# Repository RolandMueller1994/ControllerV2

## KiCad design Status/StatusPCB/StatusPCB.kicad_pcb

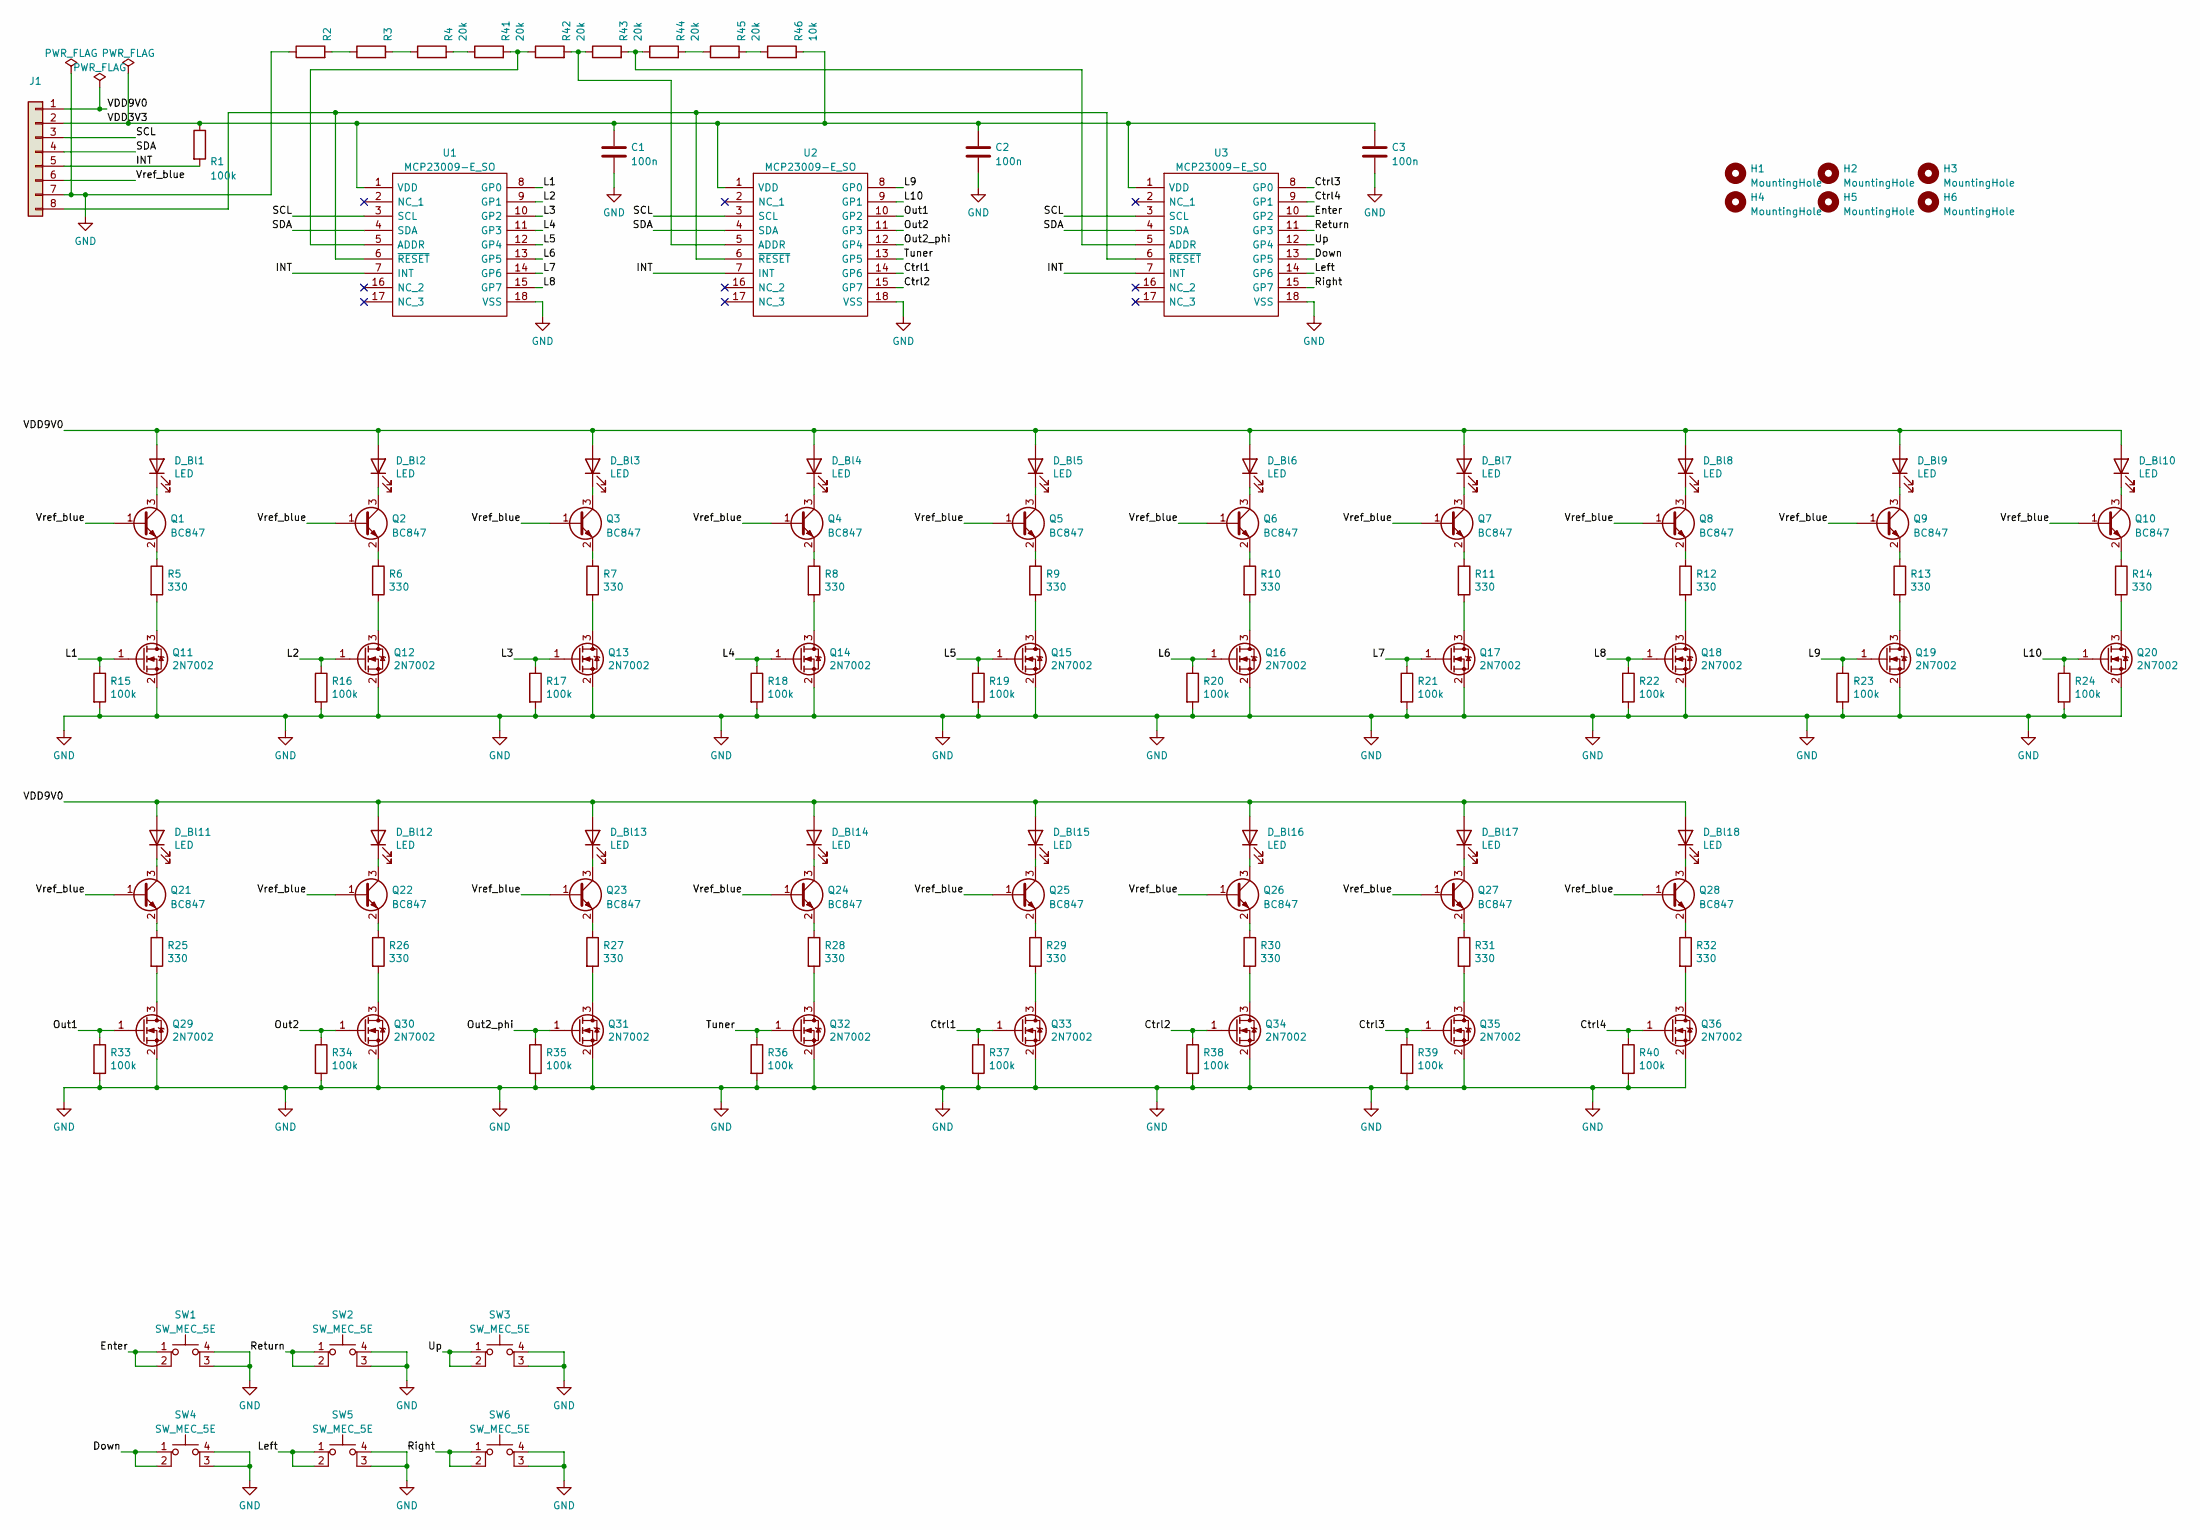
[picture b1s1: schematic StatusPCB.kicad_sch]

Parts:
C1, C2, C3: 100n; C_1206_3216Metric_Pad1.33x1.80mm_HandSolder
D_Bl1, D_Bl2, D_Bl3, D_Bl4, D_Bl5, D_Bl6, D_Bl7, D_Bl8, D_Bl9, D_Bl10, D_Bl11, D_Bl12, D_Bl13, D_Bl14, D_Bl15, D_Bl16, D_Bl17, D_Bl18: LED; LED_D3.0mm
H1, H2, H3, H4, H5, H6: MountingHole; MountingHole_3.2mm_M3
J1: (no value)
Q1, Q2, Q3, Q4, Q5, Q6, Q7, Q8, Q9, Q10, Q21, Q22, Q23, Q24, Q25, Q26, Q27, Q28: BC847; SOT-23
Q11, Q12, Q13, Q14, Q15, Q16, Q17, Q18, Q19, Q20, Q29, Q30, Q31, Q32, Q33, Q34, Q35, Q36: 2N7002; SOT-23
R1, R15, R16, R17, R18, R19, R20, R21, R22, R23, R24, R33, R34, R35, R36, R37, R38, R39, R40: 100k; R_1206_3216Metric_Pad1.30x1.75mm_HandSolder
R2, R3: R_1206_3216Metric_Pad1.30x1.75mm_HandSolder
R4, R41, R42, R43, R44, R45: 20k; R_1206_3216Metric_Pad1.30x1.75mm_HandSolder
R5, R6, R7, R8, R9, R10, R11, R12, R13, R14, R25, R26, R27, R28, R29, R30, R31, R32: 330; R_1206_3216Metric_Pad1.30x1.75mm_HandSolder
R46: 10k; R_1206_3216Metric_Pad1.30x1.75mm_HandSolder
SW1, SW2, SW3, SW4, SW5, SW6: SW_MEC_5E; SW_MEC_5GTH9
U1, U2, U3: MCP23009-E_SO; Manufacturer_Part_Number MCP23009-E/SO; Mouser Part Number 579-MCP23009-E/SO

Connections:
/Ctrl1: Q33.1 (G), R37.1, U2.14 (GP6)
/Ctrl2: Q34.1 (G), R38.1, U2.15 (GP7)
/Ctrl3: Q35.1 (G), R39.1, U3.8 (GP0)
/Ctrl4: Q36.1 (G), R40.1, U3.9 (GP1)
/Down: SW4.1, SW4.2, U3.13 (GP5)
/Enter: SW1.1, SW1.2, U3.10 (GP2)
/INT: J1.5, R1.2, U1.7 (INT), U2.7 (INT), U3.7 (INT)
/L1: Q11.1 (G), R15.1, U1.8 (GP0)
/L2: Q12.1 (G), R16.1, U1.9 (GP1)
/L3: Q13.1 (G), R17.1, U1.10 (GP2)
/L4: Q14.1 (G), R18.1, U1.11 (GP3)
/L5: Q15.1 (G), R19.1, U1.12 (GP4)
/L6: Q16.1 (G), R20.1, U1.13 (GP5)
/L7: Q17.1 (G), R21.1, U1.14 (GP6)
/L8: Q18.1 (G), R22.1, U1.15 (GP7)
/L9: Q19.1 (G), R23.1, U2.8 (GP0)
/L10: Q20.1 (G), R24.1, U2.9 (GP1)
/Left: SW5.1, SW5.2, U3.14 (GP6)
/Out1: Q29.1 (G), R33.1, U2.10 (GP2)
/Out2: Q30.1 (G), R34.1, U2.11 (GP3)
/Out2_phi: Q31.1 (G), R35.1, U2.12 (GP4)
/Return: SW2.1, SW2.2, U3.11 (GP3)
/Right: SW6.1, SW6.2, U3.15 (GP7)
/SCL: J1.3, U1.3 (SCL), U2.3 (SCL), U3.3 (SCL)
/SDA: J1.4, U1.4 (SDA), U2.4 (SDA), U3.4 (SDA)
/Tuner: Q32.1 (G), R36.1, U2.13 (GP5)
/Up: SW3.1, SW3.2, U3.12 (GP4)
/VDD3V3: C1.1, C2.1, C3.1, J1.2, R1.1, R46.2, U1.1 (VDD), U2.1 (VDD), U3.1 (VDD)
/VDD9V0: D_Bl1.2 (A), D_Bl2.2 (A), D_Bl3.2 (A), D_Bl4.2 (A), D_Bl5.2 (A), D_Bl6.2 (A), D_Bl7.2 (A), D_Bl8.2 (A), D_Bl9.2 (A), D_Bl10.2 (A), D_Bl11.2 (A), D_Bl12.2 (A), D_Bl13.2 (A), D_Bl14.2 (A), D_Bl15.2 (A), D_Bl16.2 (A), D_Bl17.2 (A), D_Bl18.2 (A), J1.1
/Vref_blue: J1.6, Q1.1 (B), Q2.1 (B), Q3.1 (B), Q4.1 (B), Q5.1 (B), Q6.1 (B), Q7.1 (B), Q8.1 (B), Q9.1 (B), Q10.1 (B), Q21.1 (B), Q22.1 (B), Q23.1 (B), Q24.1 (B), Q25.1 (B), Q26.1 (B), Q27.1 (B), Q28.1 (B)
GND: C1.2, C2.2, C3.2, J1.7, Q11.2 (S), Q12.2 (S), Q13.2 (S), Q14.2 (S), Q15.2 (S), Q16.2 (S), Q17.2 (S), Q18.2 (S), Q19.2 (S), Q20.2 (S), Q29.2 (S), Q30.2 (S), Q31.2 (S), Q32.2 (S), Q33.2 (S), Q34.2 (S), Q35.2 (S), Q36.2 (S), R2.1, R15.2, R16.2, R17.2, R18.2, R19.2, R20.2, R21.2, R22.2, R23.2, R24.2, R33.2, R34.2, R35.2, R36.2, R37.2, R38.2, R39.2, R40.2, SW1.3 (K), SW1.4 (A), SW2.3 (K), SW2.4 (A), SW3.3 (K), SW3.4 (A), SW4.3 (K), SW4.4 (A), SW5.3 (K), SW5.4 (A), SW6.3 (K), SW6.4 (A), U1.18 (VSS), U2.18 (VSS), U3.18 (VSS)
unnamed: D_Bl1.1 (K), Q1.3 (C)
unnamed: D_Bl2.1 (K), Q2.3 (C)
unnamed: D_Bl3.1 (K), Q3.3 (C)
unnamed: D_Bl4.1 (K), Q4.3 (C)
unnamed: D_Bl5.1 (K), Q5.3 (C)
unnamed: D_Bl6.1 (K), Q6.3 (C)
unnamed: D_Bl7.1 (K), Q7.3 (C)
unnamed: D_Bl8.1 (K), Q8.3 (C)
unnamed: D_Bl9.1 (K), Q9.3 (C)
unnamed: D_Bl10.1 (K), Q10.3 (C)
unnamed: D_Bl11.1 (K), Q21.3 (C)
unnamed: D_Bl12.1 (K), Q22.3 (C)
unnamed: D_Bl13.1 (K), Q23.3 (C)
unnamed: D_Bl14.1 (K), Q24.3 (C)
unnamed: D_Bl15.1 (K), Q25.3 (C)
unnamed: D_Bl16.1 (K), Q26.3 (C)
unnamed: D_Bl17.1 (K), Q27.3 (C)
unnamed: D_Bl18.1 (K), Q28.3 (C)
unnamed: J1.8, U1.6 (~RESET), U2.6 (~RESET), U3.6 (~RESET)
unnamed: Q1.2 (E), R5.1
unnamed: Q2.2 (E), R6.1
unnamed: Q3.2 (E), R7.1
unnamed: Q4.2 (E), R8.1
unnamed: Q5.2 (E), R9.1
unnamed: Q6.2 (E), R10.1
unnamed: Q7.2 (E), R11.1
unnamed: Q8.2 (E), R12.1
unnamed: Q9.2 (E), R13.1
unnamed: Q10.2 (E), R14.1
unnamed: Q11.3 (D), R5.2
unnamed: Q12.3 (D), R6.2
unnamed: Q13.3 (D), R7.2
unnamed: Q14.3 (D), R8.2
unnamed: Q15.3 (D), R9.2
unnamed: Q16.3 (D), R10.2
unnamed: Q17.3 (D), R11.2
unnamed: Q18.3 (D), R12.2
unnamed: Q19.3 (D), R13.2
unnamed: Q20.3 (D), R14.2
unnamed: Q21.2 (E), R25.1
unnamed: Q22.2 (E), R26.1
unnamed: Q23.2 (E), R27.1
unnamed: Q24.2 (E), R28.1
unnamed: Q25.2 (E), R29.1
unnamed: Q26.2 (E), R30.1
unnamed: Q27.2 (E), R31.1
unnamed: Q28.2 (E), R32.1
unnamed: Q29.3 (D), R25.2
unnamed: Q30.3 (D), R26.2
unnamed: Q31.3 (D), R27.2
unnamed: Q32.3 (D), R28.2
unnamed: Q33.3 (D), R29.2
unnamed: Q34.3 (D), R30.2
unnamed: Q35.3 (D), R31.2
unnamed: Q36.3 (D), R32.2
unnamed: R2.2, R3.1
unnamed: R3.2, R4.1
unnamed: R4.2, R41.1
unnamed: R41.2, R42.1, U1.5 (ADDR)
unnamed: R42.2, R43.1, U2.5 (ADDR)
unnamed: R43.2, R44.1, U3.5 (ADDR)
unnamed: R44.2, R45.1
unnamed: R45.2, R46.1

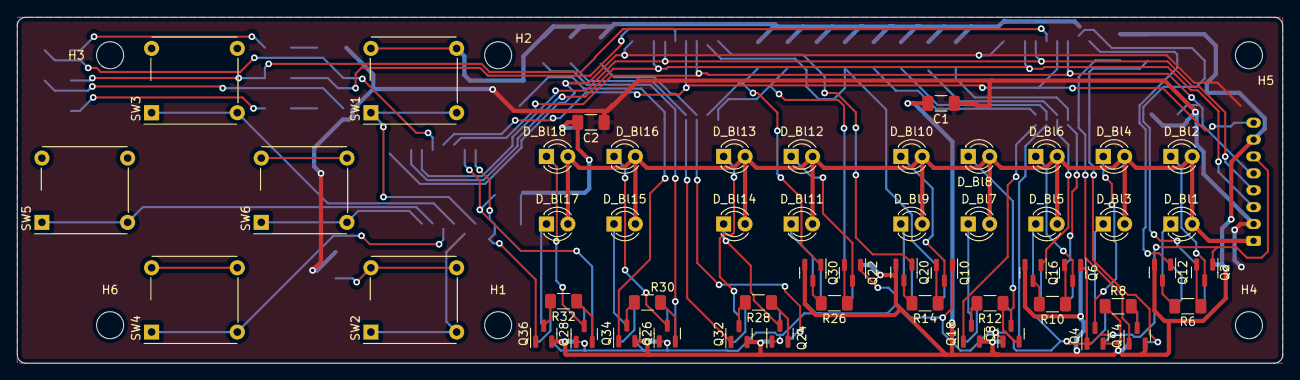
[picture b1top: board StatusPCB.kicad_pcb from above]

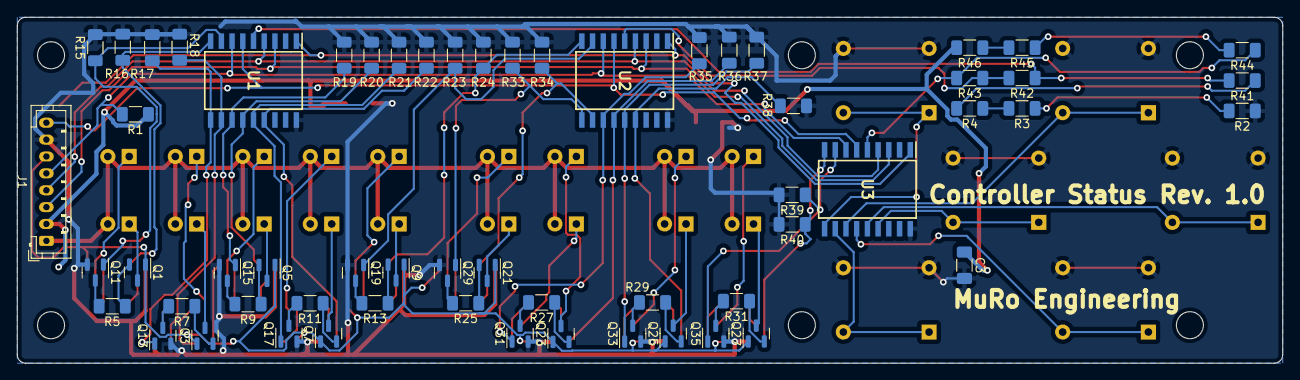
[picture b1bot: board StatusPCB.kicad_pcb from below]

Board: 2 copper layers, 150.0 x 41.0 mm, 119 parts (60 on the bottom side), 94 nets.

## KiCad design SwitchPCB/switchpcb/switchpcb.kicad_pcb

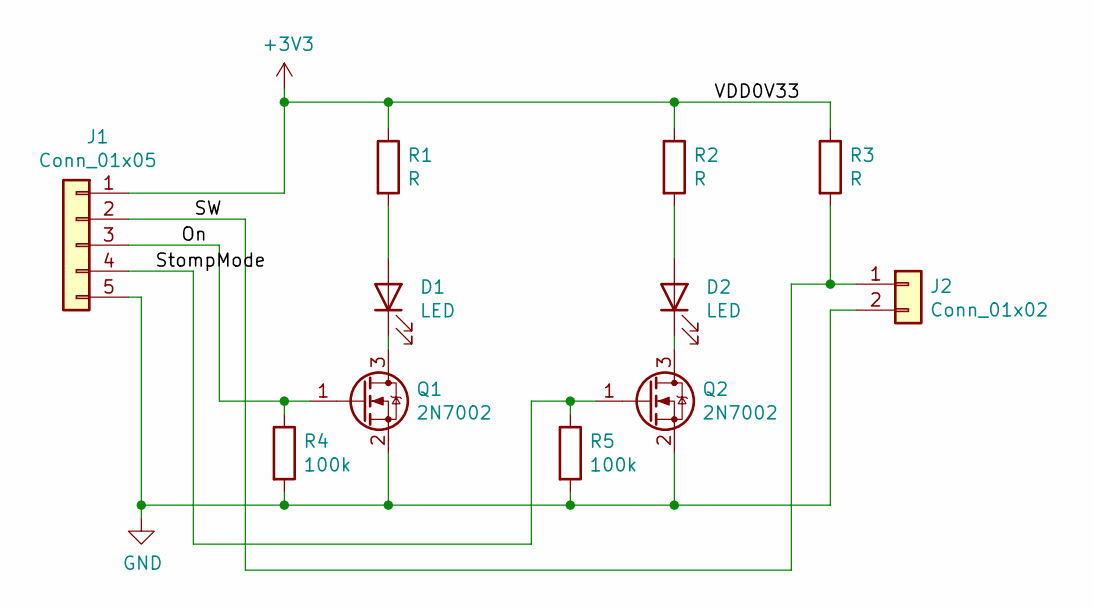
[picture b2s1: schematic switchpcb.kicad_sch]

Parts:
D1, D2: LED; LED_D3.0mm
J1: Conn_01x05; JST_PH_B5B-PH-K_1x05_P2.00mm_Vertical
J2: Conn_01x02; JST_PH_B2B-PH-K_1x02_P2.00mm_Vertical
Q1, Q2: 2N7002; SOT-23
R1, R2, R3: R; R_1206_3216Metric_Pad1.30x1.75mm_HandSolder
R4, R5: 100k; R_1206_3216Metric_Pad1.30x1.75mm_HandSolder

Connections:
+3V3: J1.1, R1.1, R2.1, R3.1
/On: J1.3, Q1.1 (G), R4.1
/SW: J1.2, J2.1, R3.2
/StompMode: J1.4, Q2.1 (G), R5.1
GND: J1.5, J2.2, Q1.2 (S), Q2.2 (S), R4.2, R5.2
unnamed: D1.1 (K), Q1.3 (D)
unnamed: D1.2 (A), R1.2
unnamed: D2.1 (K), Q2.3 (D)
unnamed: D2.2 (A), R2.2

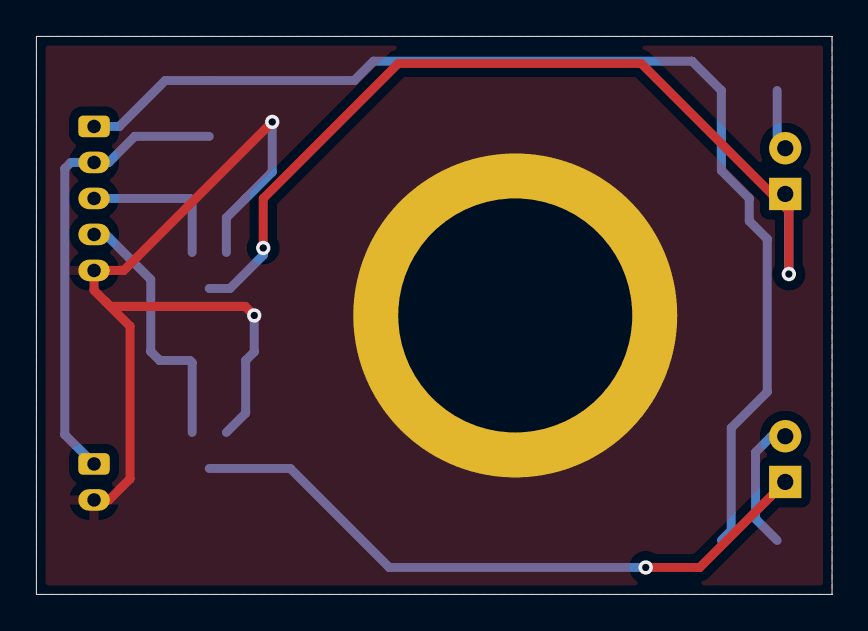
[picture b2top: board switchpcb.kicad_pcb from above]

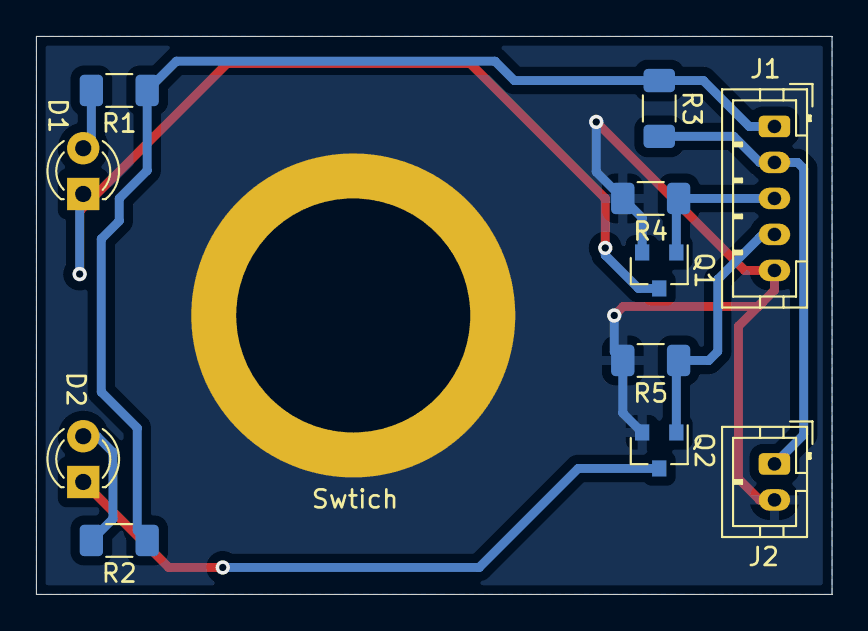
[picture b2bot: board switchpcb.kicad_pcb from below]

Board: 2 copper layers, 44.2 x 31.0 mm, 12 parts (12 on the bottom side), 9 nets.

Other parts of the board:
Swtich: LehleSwitch

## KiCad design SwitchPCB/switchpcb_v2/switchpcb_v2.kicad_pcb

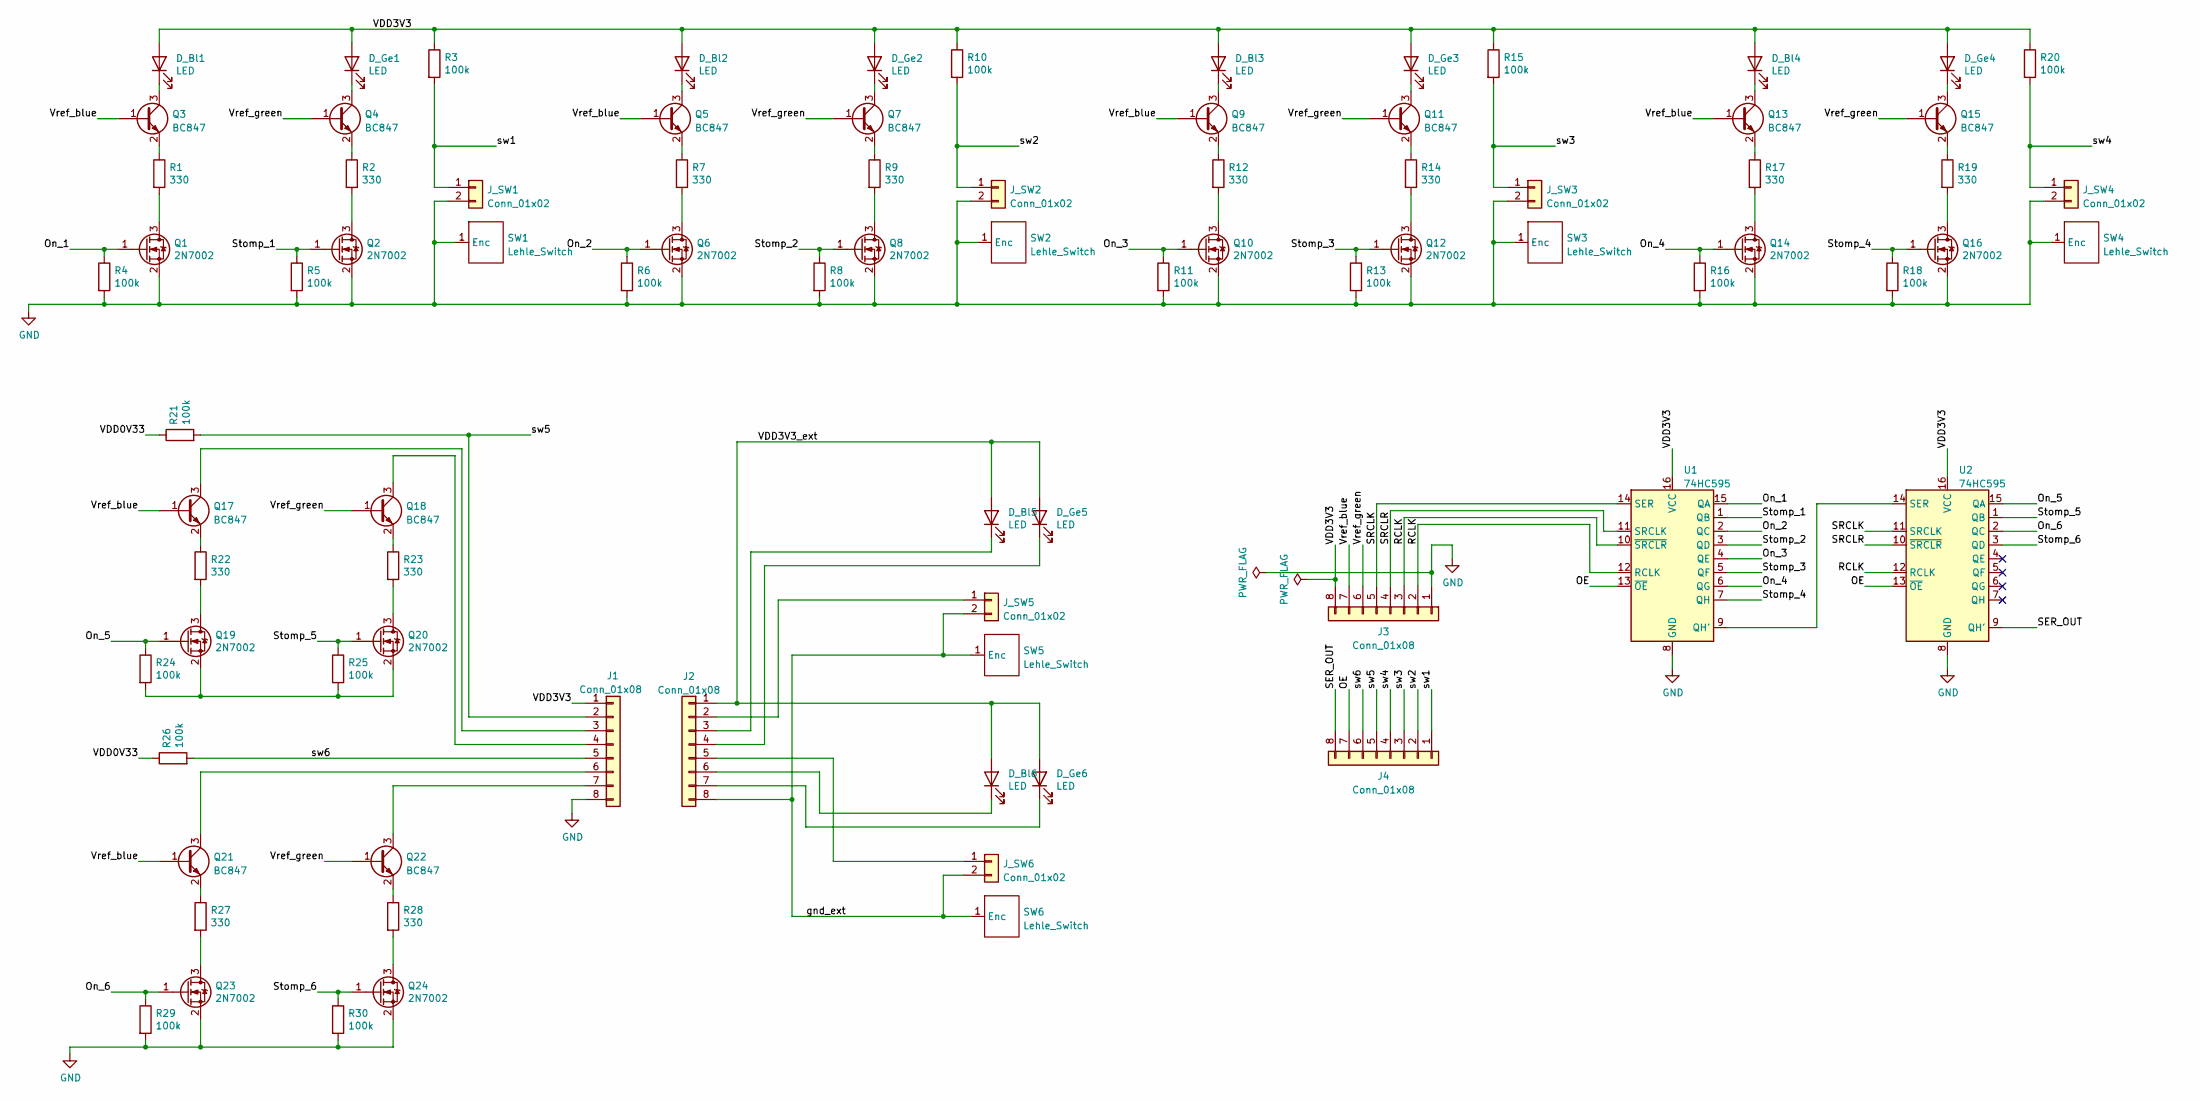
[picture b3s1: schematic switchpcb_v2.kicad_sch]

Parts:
D_Bl1, D_Bl2, D_Bl3, D_Bl4, D_Bl5, D_Bl6: LED; LED_D3.0mm
D_Ge1, D_Ge2, D_Ge3, D_Ge4, D_Ge5, D_Ge6: LED; LED_D3.0mm
J1, J2, J3, J4: Conn_01x08
J_SW1, J_SW2, J_SW3, J_SW4, J_SW5, J_SW6: Conn_01x02
Q1, Q2, Q6, Q8, Q10, Q12, Q14, Q16, Q19, Q20, Q23, Q24: 2N7002; SOT-23
Q3, Q4, Q5, Q7, Q9, Q11, Q13, Q15, Q17, Q18, Q21, Q22: BC847; SOT-23
R1, R2, R7, R9, R12, R14, R17, R19, R22, R23, R27, R28: 330; R_1206_3216Metric_Pad1.30x1.75mm_HandSolder
R3, R4, R5, R6, R8, R10, R11, R13, R15, R16, R18, R20, R21, R24, R25, R26, R29, R30: 100k; R_1206_3216Metric_Pad1.30x1.75mm_HandSolder
SW1, SW2, SW3, SW4, SW5, SW6: Lehle_Switch
U1, U2: 74HC595

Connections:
/OE: J4.7, U1.13 (~OE), U2.13 (~OE)
/On_1: Q1.1 (G), R4.1, U1.15 (QA)
/On_2: Q6.1 (G), R6.1, U1.2 (QC)
/On_3: Q10.1 (G), R11.1, U1.4 (QE)
/On_4: Q14.1 (G), R16.1, U1.6 (QG)
/On_5: Q19.1 (G), R24.1, U2.15 (QA)
/On_6: Q23.1 (G), R29.1, U2.2 (QC)
/RCLK: J3.2, J3.3, U1.10 (~SRCLR), U1.12 (RCLK), U2.12 (RCLK)
/SER_OUT: J4.8, U2.9 (QH')
/SRCLK: J3.5, U1.14 (SER), U2.11 (SRCLK)
/SRCLR: J3.4, U1.11 (SRCLK), U2.10 (~SRCLR)
/Stomp_1: Q2.1 (G), R5.1, U1.1 (QB)
/Stomp_2: Q8.1 (G), R8.1, U1.3 (QD)
/Stomp_3: Q12.1 (G), R13.1, U1.5 (QF)
/Stomp_4: Q16.1 (G), R18.1, U1.7 (QH)
/Stomp_5: Q20.1 (G), R25.1, U2.1 (QB)
/Stomp_6: Q24.1 (G), R30.1, U2.3 (QD)
/VDD0V33: R21.1, R26.1
/VDD3V3: D_Bl1.2 (A), D_Bl2.2 (A), D_Bl3.2 (A), D_Bl4.2 (A), D_Ge1.2 (A), D_Ge2.2 (A), D_Ge3.2 (A), D_Ge4.2 (A), J1.1, J3.8, R3.1, R10.1, R15.1, R20.1, U1.16 (VCC), U2.16 (VCC)
/VDD3V3_ext: D_Bl5.2 (A), D_Bl6.2 (A), D_Ge5.2 (A), D_Ge6.2 (A), J2.1
/Vref_blue: J3.7, Q3.1 (B), Q5.1 (B), Q9.1 (B), Q13.1 (B), Q17.1 (B), Q21.1 (B)
/Vref_green: J3.6, Q4.1 (B), Q7.1 (B), Q11.1 (B), Q15.1 (B), Q18.1 (B), Q22.1 (B)
/sw1: J4.1, J_SW1.1, R3.2
/sw2: J4.2, J_SW2.1, R10.2
/sw3: J4.3, J_SW3.1, R15.2
/sw4: J4.4, J_SW4.1, R20.2
/sw5: J1.2, J4.5, R21.2
/sw6: J1.5, J4.6, R26.2
unnamed: D_Bl1.1 (K), Q3.3 (C)
unnamed: D_Bl2.1 (K), Q5.3 (C)
unnamed: D_Bl3.1 (K), Q9.3 (C)
unnamed: D_Bl4.1 (K), Q13.3 (C)
unnamed: D_Bl5.1 (K), J2.3
unnamed: D_Bl6.1 (K), J2.6
unnamed: D_Ge1.1 (K), Q4.3 (C)
unnamed: D_Ge2.1 (K), Q7.3 (C)
unnamed: D_Ge3.1 (K), Q11.3 (C)
unnamed: D_Ge4.1 (K), Q15.3 (C)
unnamed: D_Ge5.1 (K), J2.4
unnamed: D_Ge6.1 (K), J2.7
unnamed: J1.3, Q17.3 (C)
unnamed: J1.4, Q18.3 (C)
unnamed: J1.6, Q21.3 (C)
unnamed: J1.7, Q22.3 (C)
unnamed: J2.2, J_SW5.1
unnamed: J2.5, J_SW6.1
unnamed: Q1.3 (D), R1.2
unnamed: Q2.3 (D), R2.2
unnamed: Q3.2 (E), R1.1
unnamed: Q4.2 (E), R2.1
unnamed: Q5.2 (E), R7.1
unnamed: Q6.3 (D), R7.2
unnamed: Q7.2 (E), R9.1
unnamed: Q8.3 (D), R9.2
unnamed: Q9.2 (E), R12.1
unnamed: Q10.3 (D), R12.2
unnamed: Q11.2 (E), R14.1
unnamed: Q12.3 (D), R14.2
unnamed: Q13.2 (E), R17.1
unnamed: Q14.3 (D), R17.2
unnamed: Q15.2 (E), R19.1
unnamed: Q16.3 (D), R19.2
unnamed: Q17.2 (E), R22.1
unnamed: Q18.2 (E), R23.1
unnamed: Q19.2 (S), Q20.2 (S), R24.2, R25.2
unnamed: Q19.3 (D), R22.2
unnamed: Q20.3 (D), R23.2
unnamed: Q21.2 (E), R27.1
unnamed: Q22.2 (E), R28.1
unnamed: Q23.3 (D), R27.2
unnamed: Q24.3 (D), R28.2
unnamed: U1.9 (QH'), U2.14 (SER)

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
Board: 2 copper layers, 84 parts (0 on the bottom side), 70 nets, no tracks yet.

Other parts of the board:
mouse-bite-2mm-slot, mouse-bite-2mm-slot#2: VAL**; mouse-bite-2mm-slot
